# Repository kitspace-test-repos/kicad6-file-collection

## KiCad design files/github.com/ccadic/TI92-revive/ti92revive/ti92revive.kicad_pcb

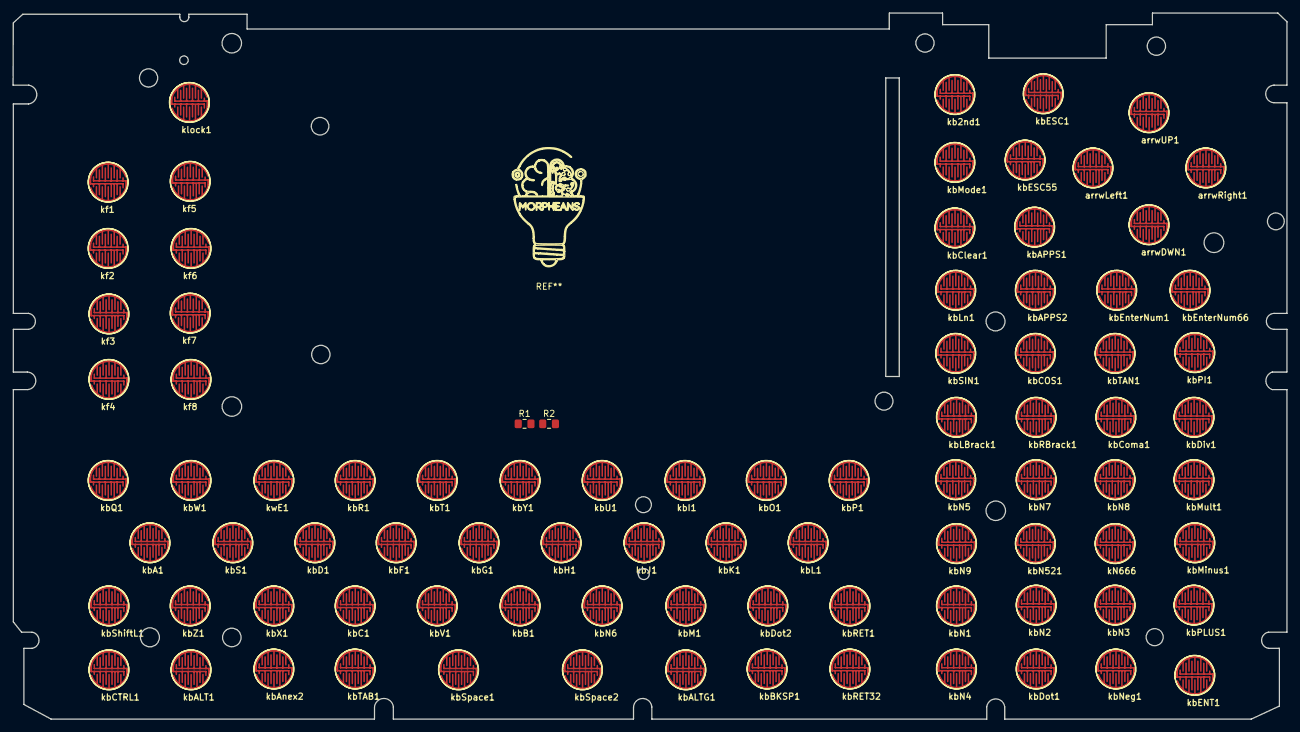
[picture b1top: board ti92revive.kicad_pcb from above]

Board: 2 copper layers, 205.0 x 113.6 mm, 88 parts (1 on the bottom side), 21 nets, no tracks yet.

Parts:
IC1: TCA8418; TCA8418-WQFN-24-1EP_4x4mm
R1: 4.7k; R_0805_2012Metric_Pad1.15x1.40mm_HandSolder
R2: 10k; R_0805_2012Metric_Pad1.15x1.40mm_HandSolder
arrwDWN1: ArwDwn; Kbpad
arrwLeft1: ArwLeft; Kbpad
arrwRight1: ArwRight; Kbpad
arrwUP1: ArwUP; Kbpad
kN666: 6; Kbpad
kb2nd1: 2ndUP; Kbpad
kbA1: A; Kbpad
kbALT1: Alt; Kbpad
kbALTG1: AltG; Kbpad
kbAPPS1, kbAPPS2: Apps; Kbpad
kbAnex2: BTN2; Kbpad
kbB1: B; Kbpad
kbBKSP1: BckSp; Kbpad
kbC1: C; Kbpad
kbCOS1: Cos; Kbpad
kbCTRL1: CTRL; Kbpad
kbClear1: Clear; Kbpad
kbComa1: Coma; Kbpad
kbD1: D; Kbpad
kbDiv1: /; Kbpad
kbDot1: .; Kbpad
kbDot2: Tet; Kbpad
kbENT1: ENTER; Kbpad
kbESC1, kbESC55: ESC; Kbpad
kbEnterNum1, kbEnterNum66: EnterN; Kbpad
kbF1: F; Kbpad
kbG1: G; Kbpad
kbH1: H; Kbpad
kbI1: I; Kbpad
kbJ1: J; Kbpad
kbK1: K; Kbpad
kbL1: L; Kbpad
kbLBrack1: (; Kbpad
kbLn1: LN; Kbpad
kbM1: M; Kbpad
kbMinus1: Minus; Kbpad
kbMode1: Mode; Kbpad
kbMult1: *; Kbpad
kbN1: 1; Kbpad
kbN2: 2; Kbpad
kbN3: 3; Kbpad
kbN4: 0; Kbpad
kbN5: 7; Kbpad
kbN6: N; Kbpad
kbN7: 8; Kbpad
kbN8: 9; Kbpad
kbN9: 4; Kbpad
kbN521: 5; Kbpad
kbNeg1: (-); Kbpad
kbO1: O; Kbpad
kbP1: P; Kbpad
kbPI1: PI; Kbpad
kbPLUS1: +; Kbpad
kbQ1: Q; Kbpad
kbR1: R; Kbpad
kbRBrack1: ); Kbpad
kbRET1, kbRET32: Return; Kbpad
kbS1: S; Kbpad
kbSIN1: Sin; Kbpad
kbShiftL1: L-Shift; Kbpad
kbSpace1, kbSpace2: Space; Kbpad
kbT1: T; Kbpad
kbTAB1: TAB; Kbpad
kbTAN1: Tan; Kbpad
kbU1: U; Kbpad
kbV1: V; Kbpad
kbW1: W; Kbpad
kbX1: X; Kbpad
kbY1: Y; Kbpad
kbZ1: Z; Kbpad
kf1: F1; Kbpad
kf2: F2; Kbpad
kf3: F3; Kbpad
kf4: F4; Kbpad
kf5: F5; Kbpad
kf6: F6; Kbpad
kf7: F7; Kbpad
kf8: F8; Kbpad
klock1: lock; Kbpad
kwE1: E; Kbpad

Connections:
/3.3v: IC1.21 (VCC), R1.2, R2.1
/col0: IC1.9 (Col0), kb2nd1.1, kbA1.1, kbCTRL1.1, kbN1.1, kbPI1.1, kbQ1.1, kbTAB1.1, klock1.1
/col1: IC1.10 (Col1), kbESC1.1, kbESC55.1, kbLBrack1.1, kbN2.1, kbS1.1, kbShiftL1.1, kbW1.1, kbZ1.1, kf1.1
/col2: IC1.11 (Col2), kbALT1.1, kbD1.1, kbMode1.1, kbN3.1, kbRBrack1.1, kbX1.1, kf2.1, kwE1.1
/col3: IC1.12 (Col3), kbC1.1, kbClear1.1, kbComa1.1, kbF1.1, kbPLUS1.1, kbR1.1, kbSpace1.1, kbSpace2.1, kf3.1
/col4: IC1.13 (Col4), kbALTG1.1, kbDiv1.1, kbG1.1, kbLn1.1, kbN4.1, kbT1.1, kbV1.1, kf4.1
/col5: IC1.14 (Col5), kbAPPS1.1, kbAPPS2.1, kbB1.1, kbDot1.1, kbH1.1, kbN5.1, kbN521.1, kbY1.1, kf5.1
/col6: IC1.15 (Col6), arrwLeft1.1, kbEnterNum1.1, kbEnterNum66.1, kbJ1.1, kbN6.1, kbN7.1, kbNeg1.1, kbU1.1, kf6.1
/col7: IC1.16 (Col7), arrwRight1.1, kbENT1.1, kbI1.1, kbK1.1, kbM1.1, kbN8.1, kbSIN1.1, kf7.1
/col8: IC1.17 (Col8), kbCOS1.1, kbDot2.1, kbL1.1, kbMinus1.1, kbMult1.1, kbO1.1, kf8.1
/col9: IC1.18 (Col9), arrwDWN1.1, kN666.1, kbAnex2.1, kbBKSP1.1, kbN9.1, kbP1.1, kbRET1.1, kbRET32.1, kbTAN1.1
/row0: IC1.8 (Row0), kN666.2, kf1.2, kf2.2, kf3.2, kf4.2, kf5.2, kf6.2, kf7.2, kf8.2, klock1.2
/row1: IC1.7 (Row1), kbI1.2, kbO1.2, kbP1.2, kbQ1.2, kbR1.2, kbT1.2, kbU1.2, kbW1.2, kbY1.2, kwE1.2
/row2: IC1.6 (Row2), kbA1.2, kbBKSP1.2, kbD1.2, kbF1.2, kbG1.2, kbH1.2, kbJ1.2, kbK1.2, kbL1.2, kbS1.2
/row3: IC1.5 (Row3), kbB1.2, kbC1.2, kbDot2.2, kbM1.2, kbN6.2, kbRET1.2, kbRET32.2, kbTAB1.2, kbV1.2, kbX1.2, kbZ1.2
/row4: IC1.4 (Row4), arrwDWN1.2, arrwLeft1.2, arrwRight1.2, arrwUP1.2, kbALT1.2, kbALTG1.2, kbCTRL1.2, kbN521.2, kbShiftL1.2, kbSpace1.2, kbSpace2.2
/row5: IC1.3 (Row5), kb2nd1.2, kbAPPS1.2, kbAPPS2.2, kbCOS1.2, kbClear1.2, kbESC1.2, kbESC55.2, kbEnterNum1.2, kbEnterNum66.2, kbLn1.2, kbMode1.2, kbSIN1.2, kbTAN1.2
/row6: IC1.2 (Row6), kbComa1.2, kbDiv1.2, kbLBrack1.2, kbMult1.2, kbN5.2, kbN7.2, kbN8.2, kbN9.2, kbPI1.2, kbRBrack1.2
/row7: IC1.1 (Row7), kbAnex2.2, kbDot1.2, kbENT1.2, kbMinus1.2, kbN1.2, kbN2.2, kbN3.2, kbN4.2, kbNeg1.2, kbPLUS1.2
INT: IC1.24 (INT), R1.1
unnamed: IC1.20 (RESET), R2.2

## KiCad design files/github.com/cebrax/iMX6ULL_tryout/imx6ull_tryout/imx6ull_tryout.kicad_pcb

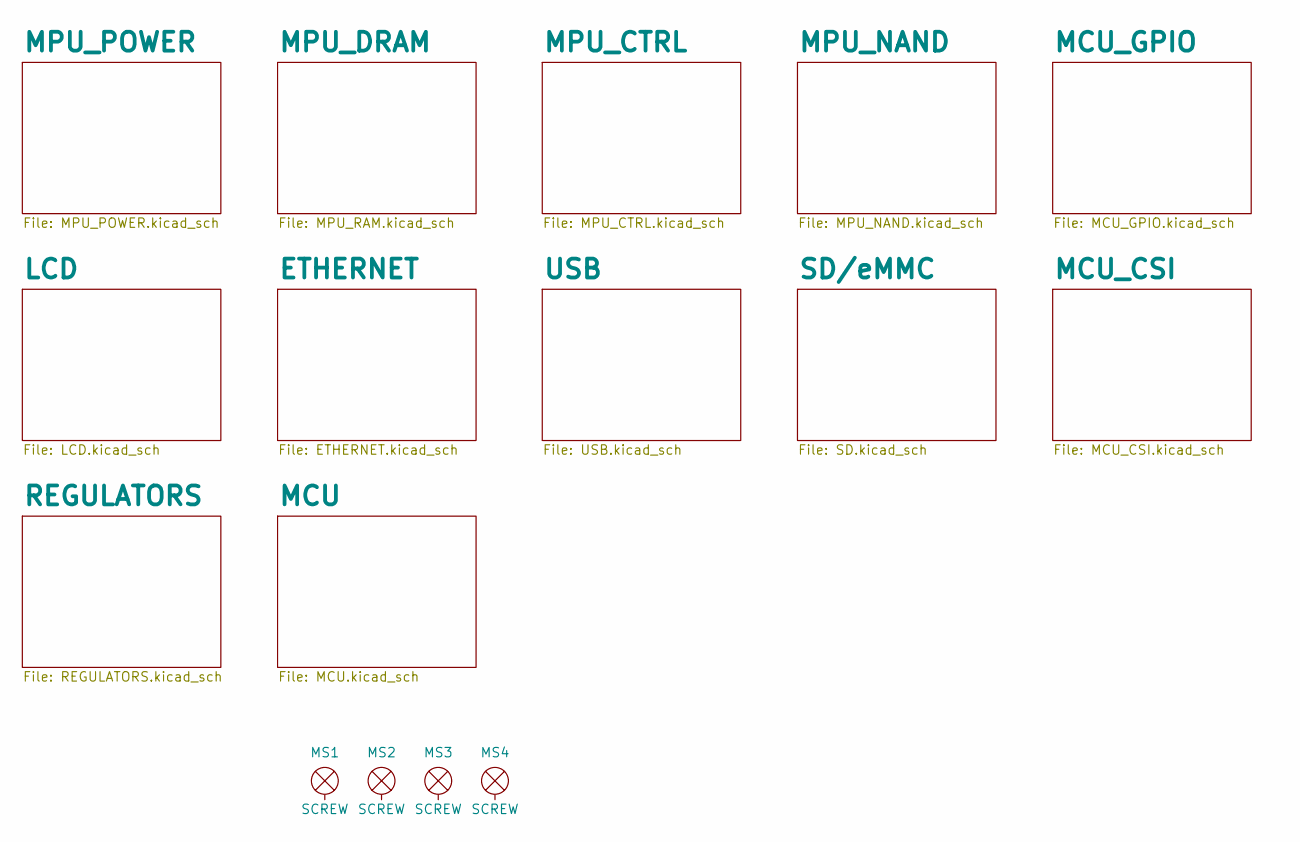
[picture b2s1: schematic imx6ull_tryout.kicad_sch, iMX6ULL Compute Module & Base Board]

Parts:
MS1, MS2, MS3, MS4: SCREW; M3-Screw-Front

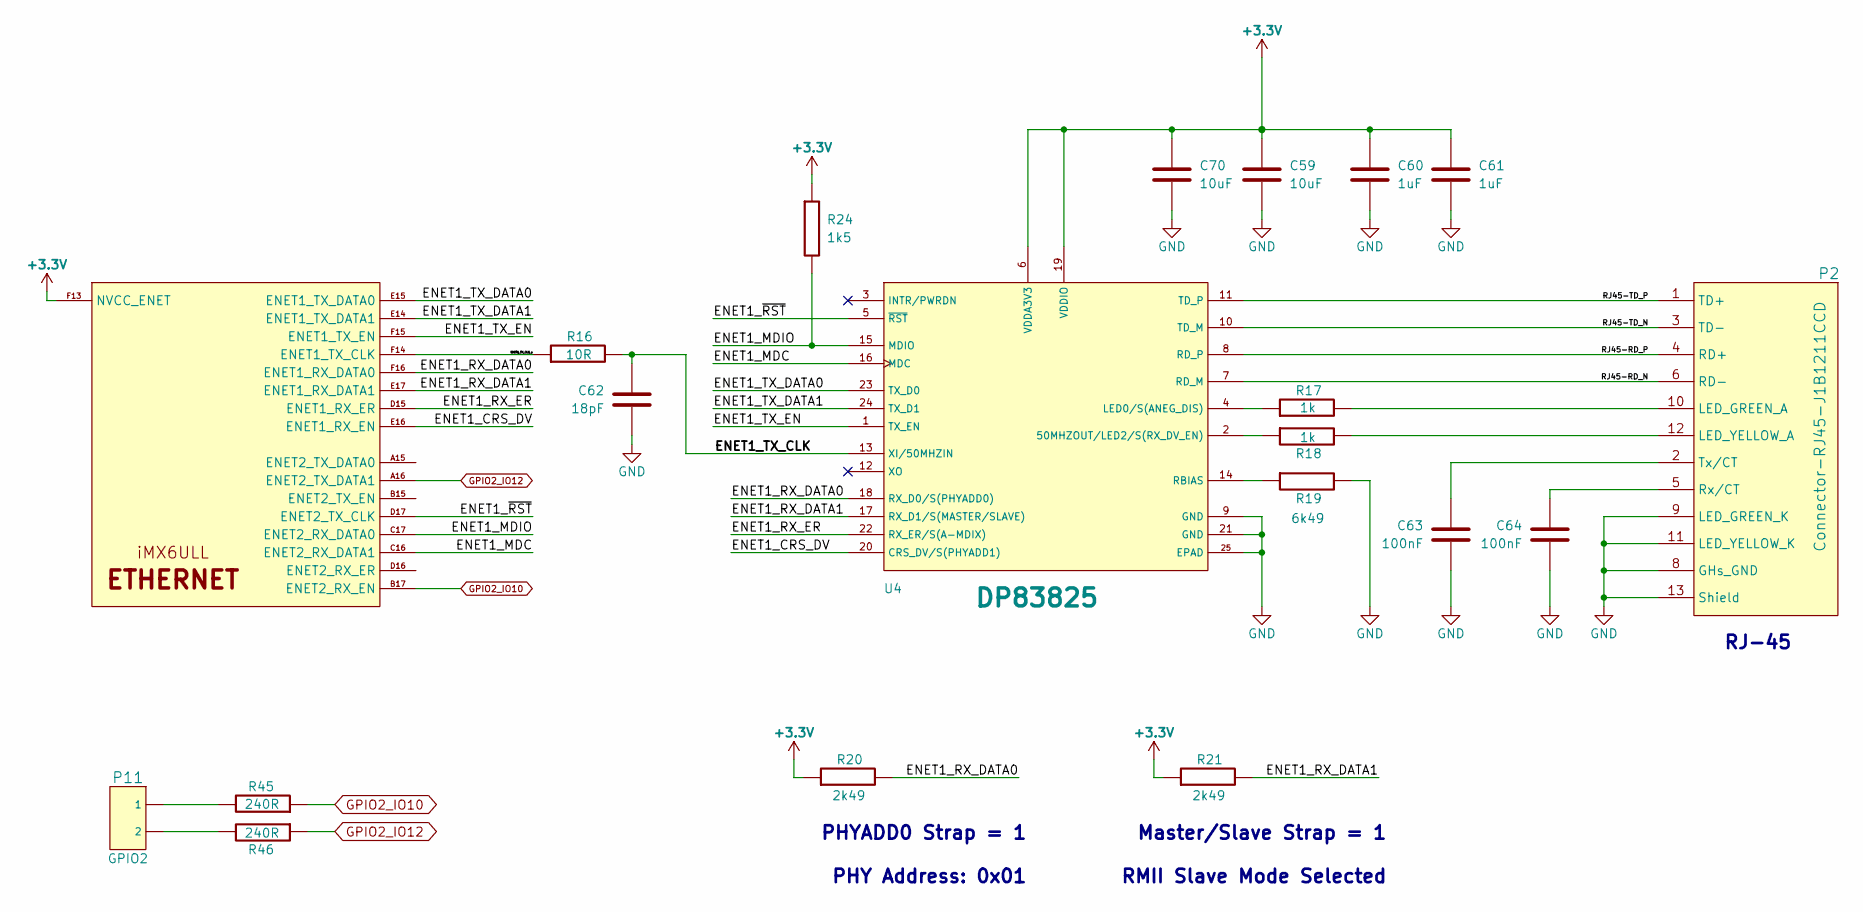
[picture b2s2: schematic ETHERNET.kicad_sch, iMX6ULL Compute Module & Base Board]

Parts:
C59, C70: 10uF; IPC-SMD-C-0402; Voltage 16V
C60, C61: 1uF; IPC-SMD-C-0402; Voltage 10V
C62: 18pF; IPC-SMD-C-0402; Voltage 50V
C63, C64: 100nF; IPC-SMD-C-0805; Voltage 50V
P2: Connector-RJ45-J1B1211CCD
P11: GPIO2; Connector-Male-Breakaway-2pins
R16: 10R; IPC-SMD-R-0402
R17, R18: 1k; IPC-SMD-R-0805
R19: 6k49; IPC-SMD-R-0603
R20, R21: 2k49; IPC-SMD-R-0603
R24: 1k5; IPC-SMD-R-0603
R45, R46: 240R; IPC-SMD-R-0402
U1: iMX6ULL; BGA289C80P17X17_1400X1400X132N
U4: DP83825; IPC-WQFN-24

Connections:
+3V3: C59.1, C60.1, C61.1, C70.1, R20.1, R21.1, R24.1, U1.F13 (NVCC_ENET), U4.6 (VDDA3V3), U4.19 (VDDIO); also elsewhere on the board
/ETHERNET/ENET1_CRS_DV: U1.E16 (ENET1_RX_EN), U4.20 (CRS_DV/S(PHYADD1))
/ETHERNET/ENET1_MDC: U1.C16 (ENET2_RX_DATA1), U4.16 (MDC)
/ETHERNET/ENET1_MDIO: R24.2, U1.C17 (ENET2_RX_DATA0), U4.15 (MDIO)
/ETHERNET/ENET1_RX_DATA0: R20.2, U1.F16 (ENET1_RX_DATA0), U4.18 (RX_D0/S(PHYADD0))
/ETHERNET/ENET1_RX_DATA1: R21.2, U1.E17 (ENET1_RX_DATA1), U4.17 (RX_D1/S(MASTER/SLAVE))
/ETHERNET/ENET1_RX_ER: U1.D15 (ENET1_RX_ER), U4.22 (RX_ER/S(A-MDIX))
/ETHERNET/ENET1_TX_CLK: C62.1, R16.2, U4.13 (XI/50MHZIN)
/ETHERNET/ENET1_TX_CLK_s: R16.1, U1.F14 (ENET1_TX_CLK)
/ETHERNET/ENET1_TX_DATA0: U1.E15 (ENET1_TX_DATA0), U4.23 (TX_D0)
/ETHERNET/ENET1_TX_DATA1: U1.E14 (ENET1_TX_DATA1), U4.24 (TX_D1)
/ETHERNET/ENET1_TX_EN: U1.F15 (ENET1_TX_EN), U4.1 (TX_EN)
/ETHERNET/ENET1_~RST: U1.D17 (ENET2_TX_CLK), U4.5 (~RST)
/ETHERNET/RJ45-RD_N: P2.6 (RD-), U4.7 (RD_M)
/ETHERNET/RJ45-RD_P: P2.4 (RD+), U4.8 (RD_P)
/ETHERNET/RJ45-TD_N: P2.3 (TD-), U4.10 (TD_M)
/ETHERNET/RJ45-TD_P: P2.1 (TD+), U4.11 (TD_P)
GND: C59.2, C60.2, C61.2, C62.2, C63.2, C64.2, C70.2, P2.8 (GHs_GND), P2.9 (LED_GREEN_K), P2.11 (LED_YELLOW_K), P2.13 (Shield), R19.2, U4.9 (GND), U4.21 (GND), U4.25 (EPAD); also elsewhere on the board
GPIO2_IO10: R45.1, U1.B17 (ENET2_RX_EN)
GPIO2_IO12: R46.1, U1.A16 (ENET2_TX_DATA1)
unnamed: C63.1, P2.2 (Tx/CT)
unnamed: C64.1, P2.5 (Rx/CT)
unnamed: P2.10 (LED_GREEN_A), R17.2
unnamed: P2.12 (LED_YELLOW_A), R18.2
unnamed: P11.1, R45.2
unnamed: P11.2, R46.2
unnamed: R17.1, U4.4 (LED0/S(ANEG_DIS))
unnamed: R18.1, U4.2 (50MHZOUT/LED2/S(RX_DV_EN))
unnamed: R19.1, U4.14 (RBIAS)

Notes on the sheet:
PHYADD0 Strap = 1 PHY Address: 0x01
Master/Slave Strap = 1 RMII Slave Mode Selected
RJ-45

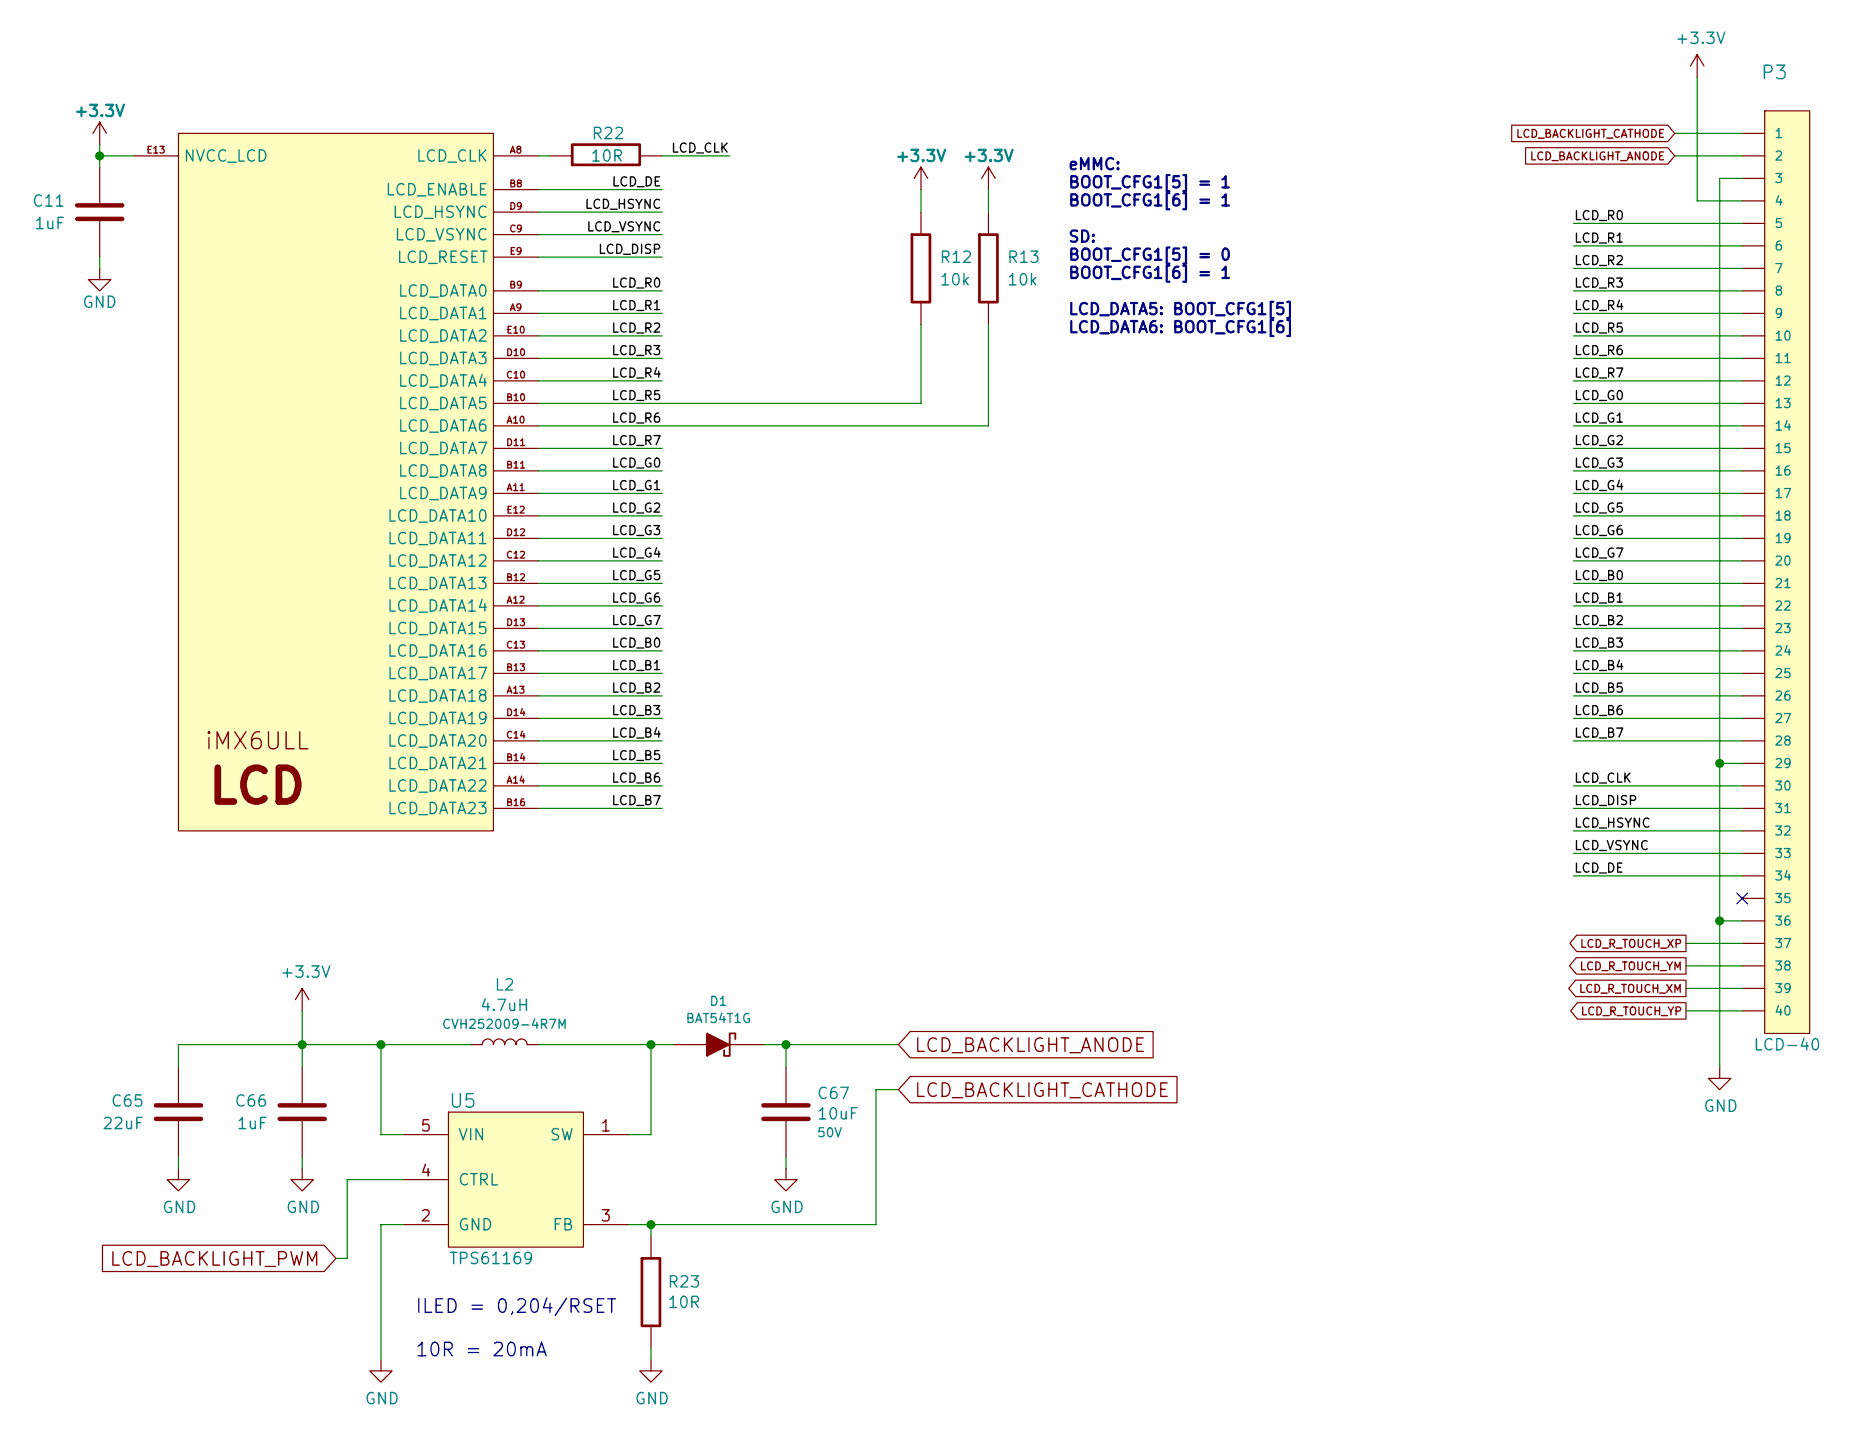
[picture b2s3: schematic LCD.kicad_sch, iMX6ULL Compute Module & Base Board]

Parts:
C11, C66: 1uF; IPC-SMD-C-0402; Voltage 10V
C65: 22uF; IPC-SMD-C-0603; Voltage 6.3V
C67: 10uF; IPC-SMD-C-1206; Voltage 50V
D1: BAT54T1G; IPC-SOD-123
L2: 4.7uH; IPC-SMD-R-0805; Part No CVH252009-4R7M
P3: LCD-40; Connector-SMD-ZIF-40-pin
R12, R13: 10k; IPC-SMD-R-0603
R22: 10R; IPC-SMD-R-0402
R23: 10R; IPC-SMD-R-0805
U1: iMX6ULL; BGA289C80P17X17_1400X1400X132N
U5: TPS61169; IPC-SC-70-5

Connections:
+3V3: C11.1, C65.1, C66.1, L2.2, P3.4, R12.1, R13.1, U1.E13 (NVCC_LCD), U5.5 (VIN); also elsewhere on the board
/LCD/LCD_B0: P3.21, U1.C13 (LCD_DATA16)
/LCD/LCD_B1: P3.22, U1.B13 (LCD_DATA17)
/LCD/LCD_B2: P3.23, U1.A13 (LCD_DATA18)
/LCD/LCD_B3: P3.24, U1.D14 (LCD_DATA19)
/LCD/LCD_B4: P3.25, U1.C14 (LCD_DATA20)
/LCD/LCD_B5: P3.26, U1.B14 (LCD_DATA21)
/LCD/LCD_B6: P3.27, U1.A14 (LCD_DATA22)
/LCD/LCD_B7: P3.28, U1.B16 (LCD_DATA23)
/LCD/LCD_CLK: P3.30, R22.2
/LCD/LCD_DE: P3.34, U1.B8 (LCD_ENABLE)
/LCD/LCD_DISP: P3.31, U1.E9 (LCD_RESET)
/LCD/LCD_G0: P3.13, U1.B11 (LCD_DATA8)
/LCD/LCD_G1: P3.14, U1.A11 (LCD_DATA9)
/LCD/LCD_G2: P3.15, U1.E12 (LCD_DATA10)
/LCD/LCD_G3: P3.16, U1.D12 (LCD_DATA11)
/LCD/LCD_G4: P3.17, U1.C12 (LCD_DATA12)
/LCD/LCD_G5: P3.18, U1.B12 (LCD_DATA13)
/LCD/LCD_G6: P3.19, U1.A12 (LCD_DATA14)
/LCD/LCD_G7: P3.20, U1.D13 (LCD_DATA15)
/LCD/LCD_HSYNC: P3.32, U1.D9 (LCD_HSYNC)
/LCD/LCD_R0: P3.5, U1.B9 (LCD_DATA0)
/LCD/LCD_R1: P3.6, U1.A9 (LCD_DATA1)
/LCD/LCD_R2: P3.7, U1.E10 (LCD_DATA2)
/LCD/LCD_R3: P3.8, U1.D10 (LCD_DATA3)
/LCD/LCD_R4: P3.9, U1.C10 (LCD_DATA4)
/LCD/LCD_R5: P3.10, R12.2, U1.B10 (LCD_DATA5)
/LCD/LCD_R6: P3.11, R13.2, U1.A10 (LCD_DATA6)
/LCD/LCD_R7: P3.12, U1.D11 (LCD_DATA7)
/LCD/LCD_VSYNC: P3.33, U1.C9 (LCD_VSYNC)
GND: C11.2, C65.2, C66.2, C67.2, P3.3, P3.29, P3.36, R23.2, U5.2 (GND); also elsewhere on the board
LCD_BACKLIGHT_ANODE: C67.1, D1.2 (K), P3.2
LCD_BACKLIGHT_CATHODE: P3.1, R23.1, U5.3 (FB)
LCD_BACKLIGHT_PWM: U5.4 (CTRL); also elsewhere on the board
LCD_R_TOUCH_XM: P3.39; also elsewhere on the board
LCD_R_TOUCH_XP: P3.37; also elsewhere on the board
LCD_R_TOUCH_YM: P3.38; also elsewhere on the board
LCD_R_TOUCH_YP: P3.40; also elsewhere on the board
unnamed: D1.1 (A), L2.1, U5.1 (SW)
unnamed: R22.1, U1.A8 (LCD_CLK)

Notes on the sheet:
ILED = 0,204/RSET 10R = 20mA
eMMC: BOOT_CFG1[5] = 1 BOOT_CFG1[6] = 1 SD: BOOT_CFG1[5] = 0 BOOT_CFG1[6] = 1 LCD_DATA5: BOOT_CFG1[5] LCD_DATA6: BOOT_CFG1[6]

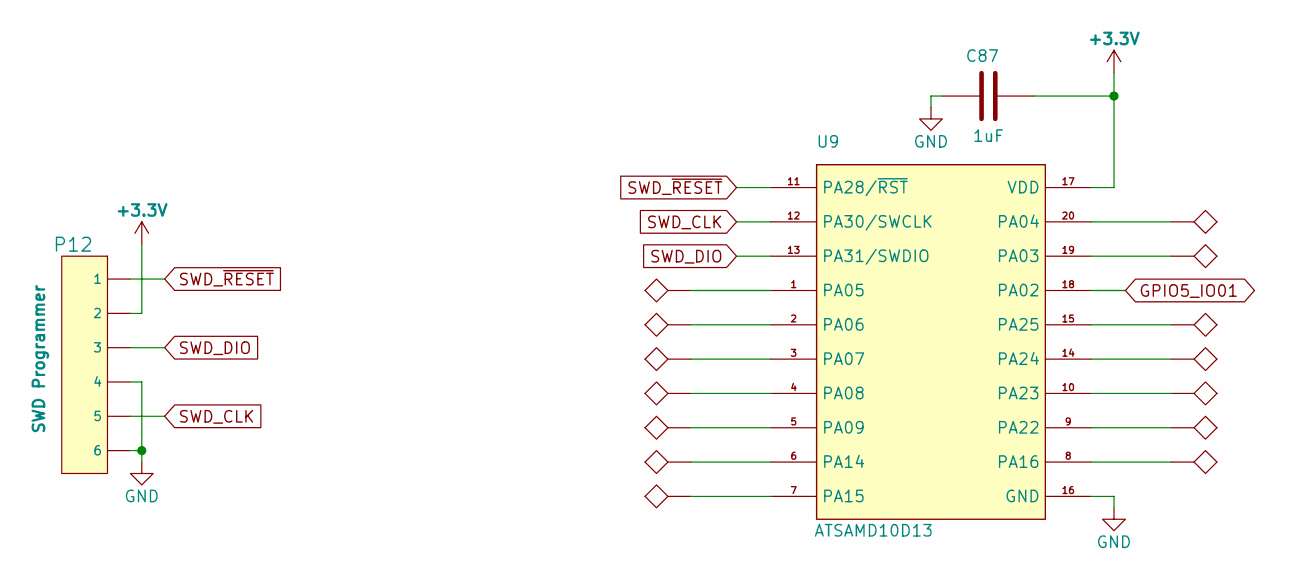
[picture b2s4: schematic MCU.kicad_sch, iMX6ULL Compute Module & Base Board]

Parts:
C87: 1uF; IPC-SMD-C-0402
P12: SWD Programmer; TC2030-IDC-NL-FP-6-pin
TP1, TP2, TP3, TP4, TP5, TP6, TP7, TP8, TP9, TP10, TP11, TP12, TP13, TP14: TEST_POINT; TP-40th-Without-Silkscreen
U9: ATSAMD10D13; IPC-SOIC-20

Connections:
+3V3: C87.1, P12.2, U9.17 (VDD); also elsewhere on the board
GND: C87.2, P12.4, P12.6, U9.16 (GND); also elsewhere on the board
GPIO5_IO01: U9.18 (PA02); also elsewhere on the board
unnamed: TP9.1, U9.3 (PA07)
unnamed: TP10.1, U9.10 (PA23)
unnamed: TP11.1, U9.4 (PA08)
unnamed: TP13.1, U9.1 (PA05)
unnamed: TP14.1, U9.2 (PA06)
unnamed: TP2.1, U9.5 (PA09)
unnamed: TP4.1, U9.6 (PA14)
unnamed: TP6.1, U9.7 (PA15)
unnamed: TP7.1, U9.8 (PA16)
unnamed: TP8.1, U9.9 (PA22)
unnamed: TP5.1, U9.14 (PA24)
unnamed: TP3.1, U9.15 (PA25)
unnamed: TP12.1, U9.19 (PA03)
unnamed: TP1.1, U9.20 (PA04)
SWD_CLK: P12.5, U9.12 (PA30/SWCLK)
SWD_DIO: P12.3, U9.13 (PA31/SWDIO)
SWD_~RESET: P12.1, U9.11 (PA28/~RST)

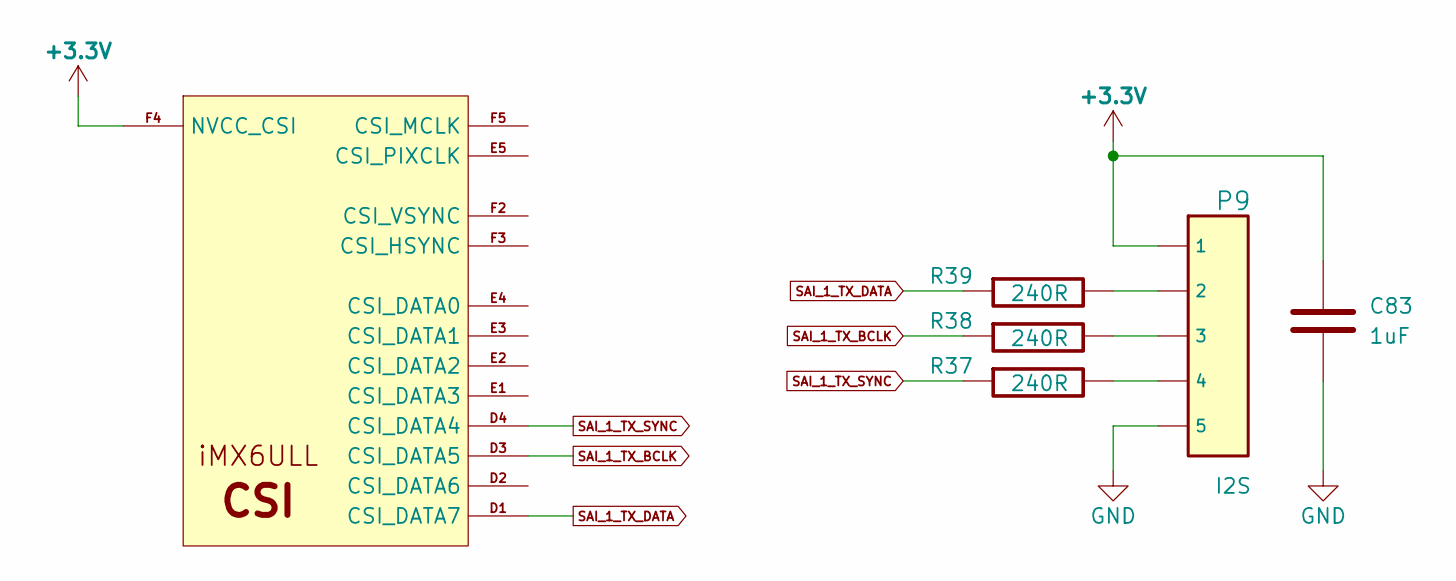
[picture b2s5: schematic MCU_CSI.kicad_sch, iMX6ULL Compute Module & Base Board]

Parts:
C83: 1uF; IPC-SMD-C-0402; Voltage 10V
P9: I2S; Connector-Male-Breakaway-5pins
R37, R38, R39: 240R; IPC-SMD-R-0402
U1: iMX6ULL; BGA289C80P17X17_1400X1400X132N

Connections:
+3V3: C83.1, P9.1, U1.F4 (NVCC_CSI); also elsewhere on the board
GND: C83.2, P9.5; also elsewhere on the board
unnamed: P9.2, R39.2
unnamed: P9.3, R38.2
unnamed: P9.4, R37.2
SAI_1_TX_BCLK: R38.1, U1.D3 (CSI_DATA5)
SAI_1_TX_DATA: R39.1, U1.D1 (CSI_DATA7)
SAI_1_TX_SYNC: R37.1, U1.D4 (CSI_DATA4)

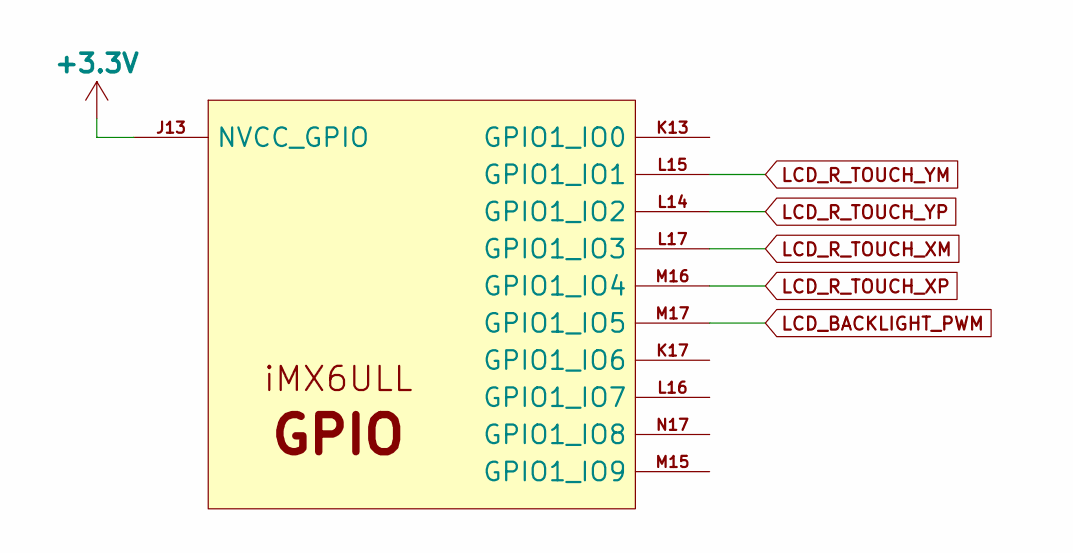
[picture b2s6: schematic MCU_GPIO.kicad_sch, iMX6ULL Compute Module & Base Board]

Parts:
U1: iMX6ULL; BGA289C80P17X17_1400X1400X132N

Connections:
+3V3: U1.J13 (NVCC_GPIO); also elsewhere on the board
LCD_BACKLIGHT_PWM: U1.M17 (GPIO1_IO5); also elsewhere on the board
LCD_R_TOUCH_XM: U1.L17 (GPIO1_IO3); also elsewhere on the board
LCD_R_TOUCH_XP: U1.M16 (GPIO1_IO4); also elsewhere on the board
LCD_R_TOUCH_YM: U1.L15 (GPIO1_IO1); also elsewhere on the board
LCD_R_TOUCH_YP: U1.L14 (GPIO1_IO2); also elsewhere on the board

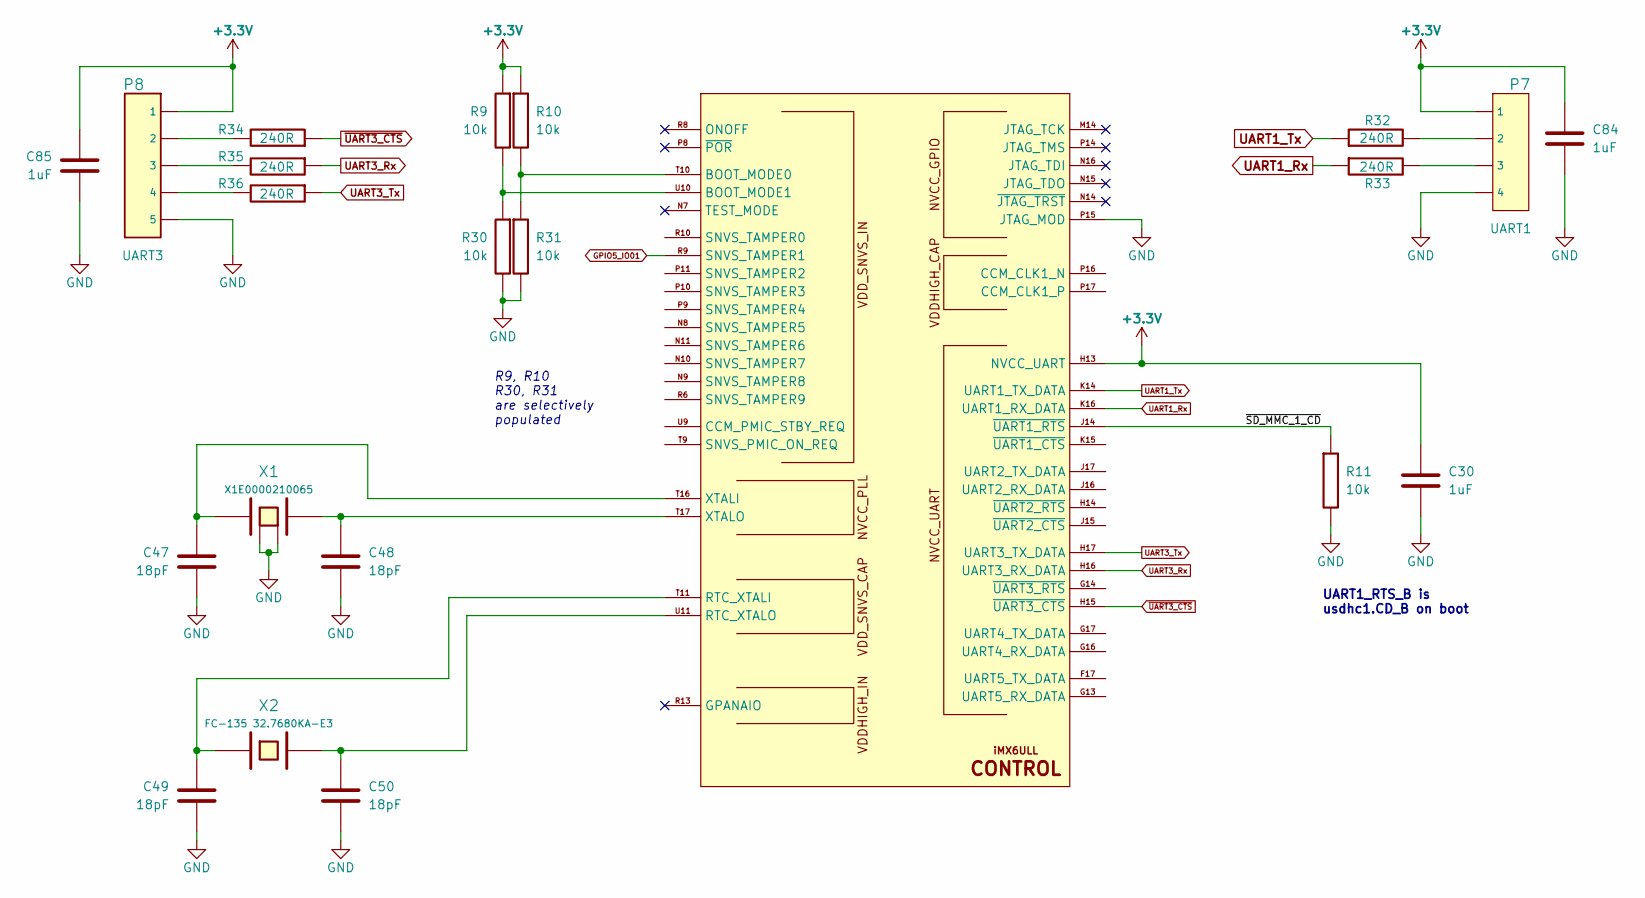
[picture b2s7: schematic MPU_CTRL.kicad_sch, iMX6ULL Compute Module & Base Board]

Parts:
C30, C84, C85: 1uF; IPC-SMD-C-0402; Voltage 10V
C47, C48, C49, C50: 18pF; IPC-SMD-C-0402; Voltage 50V
P7: UART1; Connector-Male-Breakaway-4pins
P8: UART3; Connector-Male-Breakaway-5pins
R9, R10, R11, R30, R31: 10k; IPC-SMD-R-0402
R32, R33, R34, R35, R36: 240R; IPC-SMD-R-0402
U1: iMX6ULL; BGA289C80P17X17_1400X1400X132N
X1: X1E0000210065; XTAL-SMD-3.2mm-2.5mm
X2: FC-135 32.7680KA-E3; CRYSTAL-EPSON-FC-135

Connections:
+3V3: C30.1, C84.1, C85.1, P7.1, P8.1, R9.1, R10.1, U1.H13 (NVCC_UART); also elsewhere on the board
/MPU_CTRL/~SD_MMC_1_CD: R11.1, U1.J14 (~UART1_RTS~)
GND: C30.2, C47.2, C48.2, C49.2, C50.2, C84.2, C85.2, P7.4, P8.5, R11.2, R30.2, R31.2, U1.P15 (JTAG_MOD), X1.2 (Case), X1.4 (Case); also elsewhere on the board
GPIO5_IO01: U1.R9 (SNVS_TAMPER1); also elsewhere on the board
unnamed: C47.1, U1.T16 (XTALI), X1.3
unnamed: C48.1, U1.T17 (XTALO), X1.1
unnamed: C49.1, U1.T11 (RTC_XTALI), X2.1
unnamed: C50.1, U1.U11 (RTC_XTALO), X2.2
unnamed: P7.2, R32.2
unnamed: P7.3, R33.2
unnamed: P8.2, R34.2
unnamed: P8.3, R35.2
unnamed: P8.4, R36.2
unnamed: R10.2, R31.1, U1.T10 (BOOT_MODE0)
unnamed: R9.2, R30.1, U1.U10 (BOOT_MODE1)
UART1_Rx: R33.1, U1.K16 (UART1_RX_DATA)
UART1_Tx: R32.1, U1.K14 (UART1_TX_DATA)
UART3_Rx: R35.1, U1.H16 (UART3_RX_DATA)
UART3_Tx: R36.1, U1.H17 (UART3_TX_DATA)
~UART3_CTS: R34.1, U1.H15 (~UART3_CTS~)

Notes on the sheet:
R9, R10 R30, R31 are selectively populated
UART1_RTS_B is usdhc1.CD_B on boot
